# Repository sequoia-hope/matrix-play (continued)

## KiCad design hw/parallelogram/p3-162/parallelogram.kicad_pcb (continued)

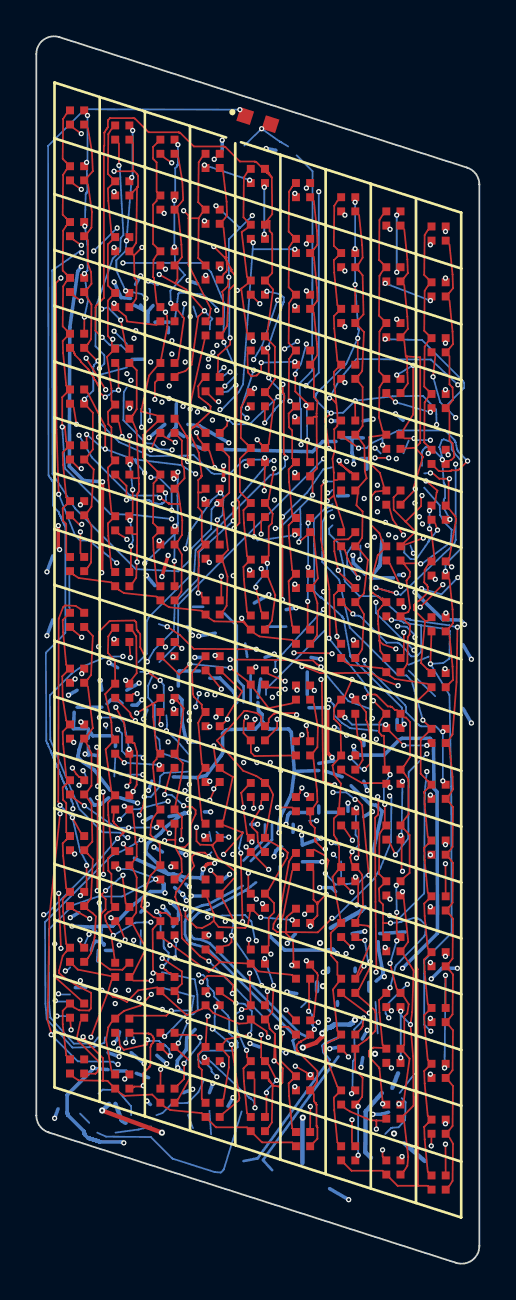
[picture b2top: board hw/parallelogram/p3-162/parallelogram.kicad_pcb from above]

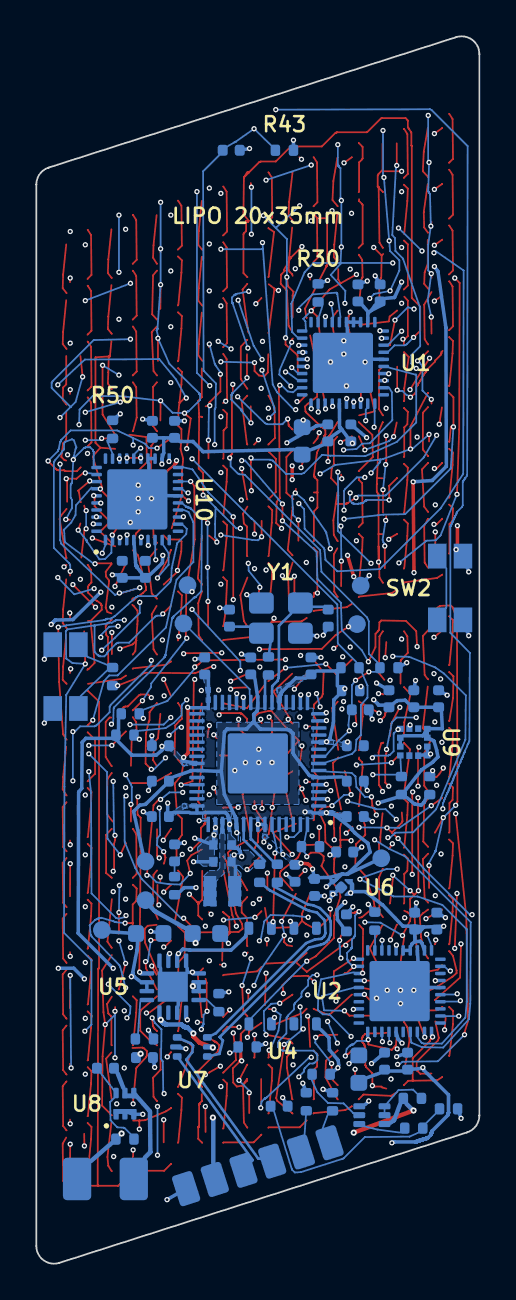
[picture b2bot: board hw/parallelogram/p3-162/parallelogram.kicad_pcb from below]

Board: 4 copper layers, 25.0 x 69.3 mm, 257 parts (94 on the bottom side), 134 nets.

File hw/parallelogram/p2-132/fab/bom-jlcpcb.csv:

Comment,Designator,Footprint,LCSC Part #,MPN,Manufacturer
1u,"C1,C3,C4,C31,C34,C41,C44",C_0402_1005Metric,C52923,CL05A105KA5NQNC,Samsung Electro-Mechanics
22u,"C2,C30,C40",C_0603_1608Metric,C86295,CL10A226MP8NUNE,Samsung Electro-Mechanics
10u,C5,C_0603_1608Metric,C19702,CL10A106KP8NNNC,Samsung Electro-Mechanics
100n,"C6,C7,C8,C9,C10,C11,C12,C13,C14,C20,C21,C22,C25,C27,C32,C33,C35,C42,C43,C70",C_0402_1005Metric,C1525,CL05B104KO5NNNC,Samsung Electro-Mechanics
4.7u,"C16,C18",C_0402_1005Metric_small_pads,C23733,CL05A475MP5NRNC,Samsung Electro-Mechanics
4.7u,"C17,C19,C26",C_0402_1005Metric,C23733,CL05A475MP5NRNC,Samsung Electro-Mechanics
15p,"C23,C24",C_0402_1005Metric,C1548,0402CG150J500NT,FH
RGB,"D1,D2,D3,D4,D5,D6,D7,D8,D9,D10,D11,D12,D13,D14,D15,D16,D17,D18,D19,D20,D21,D22,D23,D24,D25,D26,D27,D28,D29,D30,D31,D32,D33,D34,D35,D36,D37,D38,D39,D40,D41,D42,D43,D44,D45,D46,D47,D48,D49,D50,D51,D52,D53,D54,D55,D56,D57,D58,D59,D60,D61,D62,D63,D64,D65,D66,D67,D68,D69,D70,D71,D72,D73,D74,D75,D76,D77,D78,D79,D80,D81,D82,D83,D84,D85,D86,D87,D88,D89,D90,D91,D92,D93,D94,D95,D96,D97,D98,D99,D100,D101,D102,D103,D104,D105,D106,D107,D108,D109,D110,D111,D112,D113,D114,D115,D116,D117,D118,D119,D120,D121,D122,D123,D124,D125,D126,D127,D128,D129,D130,D131,D132",LED_XL-1615RGBC,C965840,XL-1615RGBC-RF,XINGLIGHT
3.3u,L1,L_pol_2016,C42411119,AOTA-B201610S3R3-101-T,Abracon
NTZD3155C,Q1,SOT-563,C236117,NTZD3155CT1G,onsemi
XYC-PT19C-L1,Q2,SENSOR_ALS-PT19,C2693594,XYC-PT19C-L1,NEWOPTO
5.1k,"R1,R2",R_0402_1005Metric,C25905,0402WGF5101TCE,UNI-ROYAL
10k,R3,R_0402_1005Metric,C25744,0402WGF1002TCE,UNI-ROYAL
3k,R4,R_0402_1005Metric,C25784,0402WGF3001TCE,UNI-ROYAL
3.6k,R5,R_0402_1005Metric,C25891,0402WGF3601TCE,UNI-ROYAL
100k,"R6,R7,R9,R10,R11,R12,R31",R_0402_1005Metric,C25741,0402WGF1003TCE,UNI-ROYAL
100R,R8,R_0402_1005Metric,C25076,0402WGF1000TCE,UNI-ROYAL
33R,R13,R_0402_1005Metric,C25105,0402WGF330JTCE,UNI-ROYAL
27R,"R14,R15",R_0402_1005Metric,C25100,0402WGF270JTCE,UNI-ROYAL
1k,"R16,R17,R18,R21,R22",R_0402_1005Metric,C11702,0402WGF1001TCE,UNI-ROYAL
4.7k,"R19,R20",R_0402_1005Metric,C25900,0402WGF4701TCE,UNI-ROYAL
30k,"R30,R33",R_0402_1005Metric,C25776,0402WGF3002TCE,UNI-ROYAL
22k,R43,R_0402_1005Metric,C25768,0402WGF2202TCE,UNI-ROYAL
USER / WAKE,SW1,SW_Panasonic_EVQP7J,C2828254,EVQP7J01P,PANASONIC
BOOTSEL,SW2,SW_Panasonic_EVQP7J,C2828254,EVQP7J01P,PANASONIC
AW20198QNR,"U1,U2",AW20198_QFN-40-1EP_5x5mm_P0.4mm_EP3.4x3.4mm,C5137654,AW20198QNR,Shanghai Awinic Tech
RP2350A,U3,RP2350-QFN-60-1EP_7x7_P0.4mm_EP3.4x3.4mm_ThermalVias,C42411118,RP2350A,Raspberry Pi
W25Q128JVPIQ,U4,WSON-8_6x5mm_P1.27mm_NoEPCopper,C190862,W25Q128JVPIQ,Winbond
BQ24073,U5,QFN-16-1EP_3x3mm_P0.5mm_EP1.7x1.7mm,C15220,BQ24073RGTR,Texas Instruments
TPS7A0233,U6,Texas_X2SON-4_1x1mm_P0.65mm,C2860046,TPS7A0233PDQNR,Texas Instruments
USBLC6-2P6,U7,SOT-666,C15999,USBLC6-2P6,STMicroelectronics
XB9901A,U8,XySemi_DFN-6_1.8x1.4mm,C669687,XB9901A,XySemi
LIS2DW12,U9,LGA-12_2x2mm_P0.5mm,C189624,LIS2DW12TR,STMicroelectronics
12MHz,Y1,Crystal_SMD_3225-4Pin_3.2x2.5mm,C20625731,ABM8-272-T3,Abracon

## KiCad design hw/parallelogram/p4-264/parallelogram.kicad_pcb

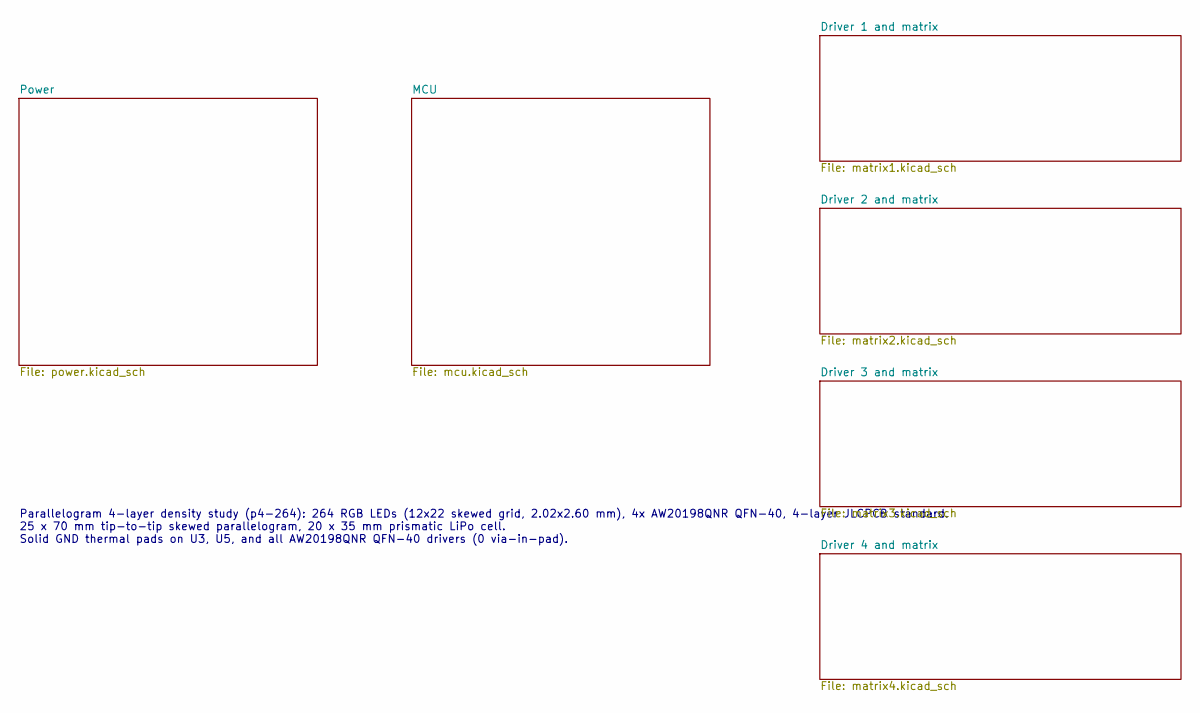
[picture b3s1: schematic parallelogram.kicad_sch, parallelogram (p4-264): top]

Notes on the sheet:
Parallelogram 4-layer density study (p4-264): 264 RGB LEDs (12x22 skewed grid, 2.02x2.60 mm), 4x AW20198QNR QFN-40, 4-layer JLCPCB standard. 25 x 70 mm tip-to-tip skewed parallelogram, 20 x 35 mm prismatic LiPo cell. Solid GND thermal pads on U3, U5, and all AW20198QNR QFN-40 drivers (0 via-in-pad).

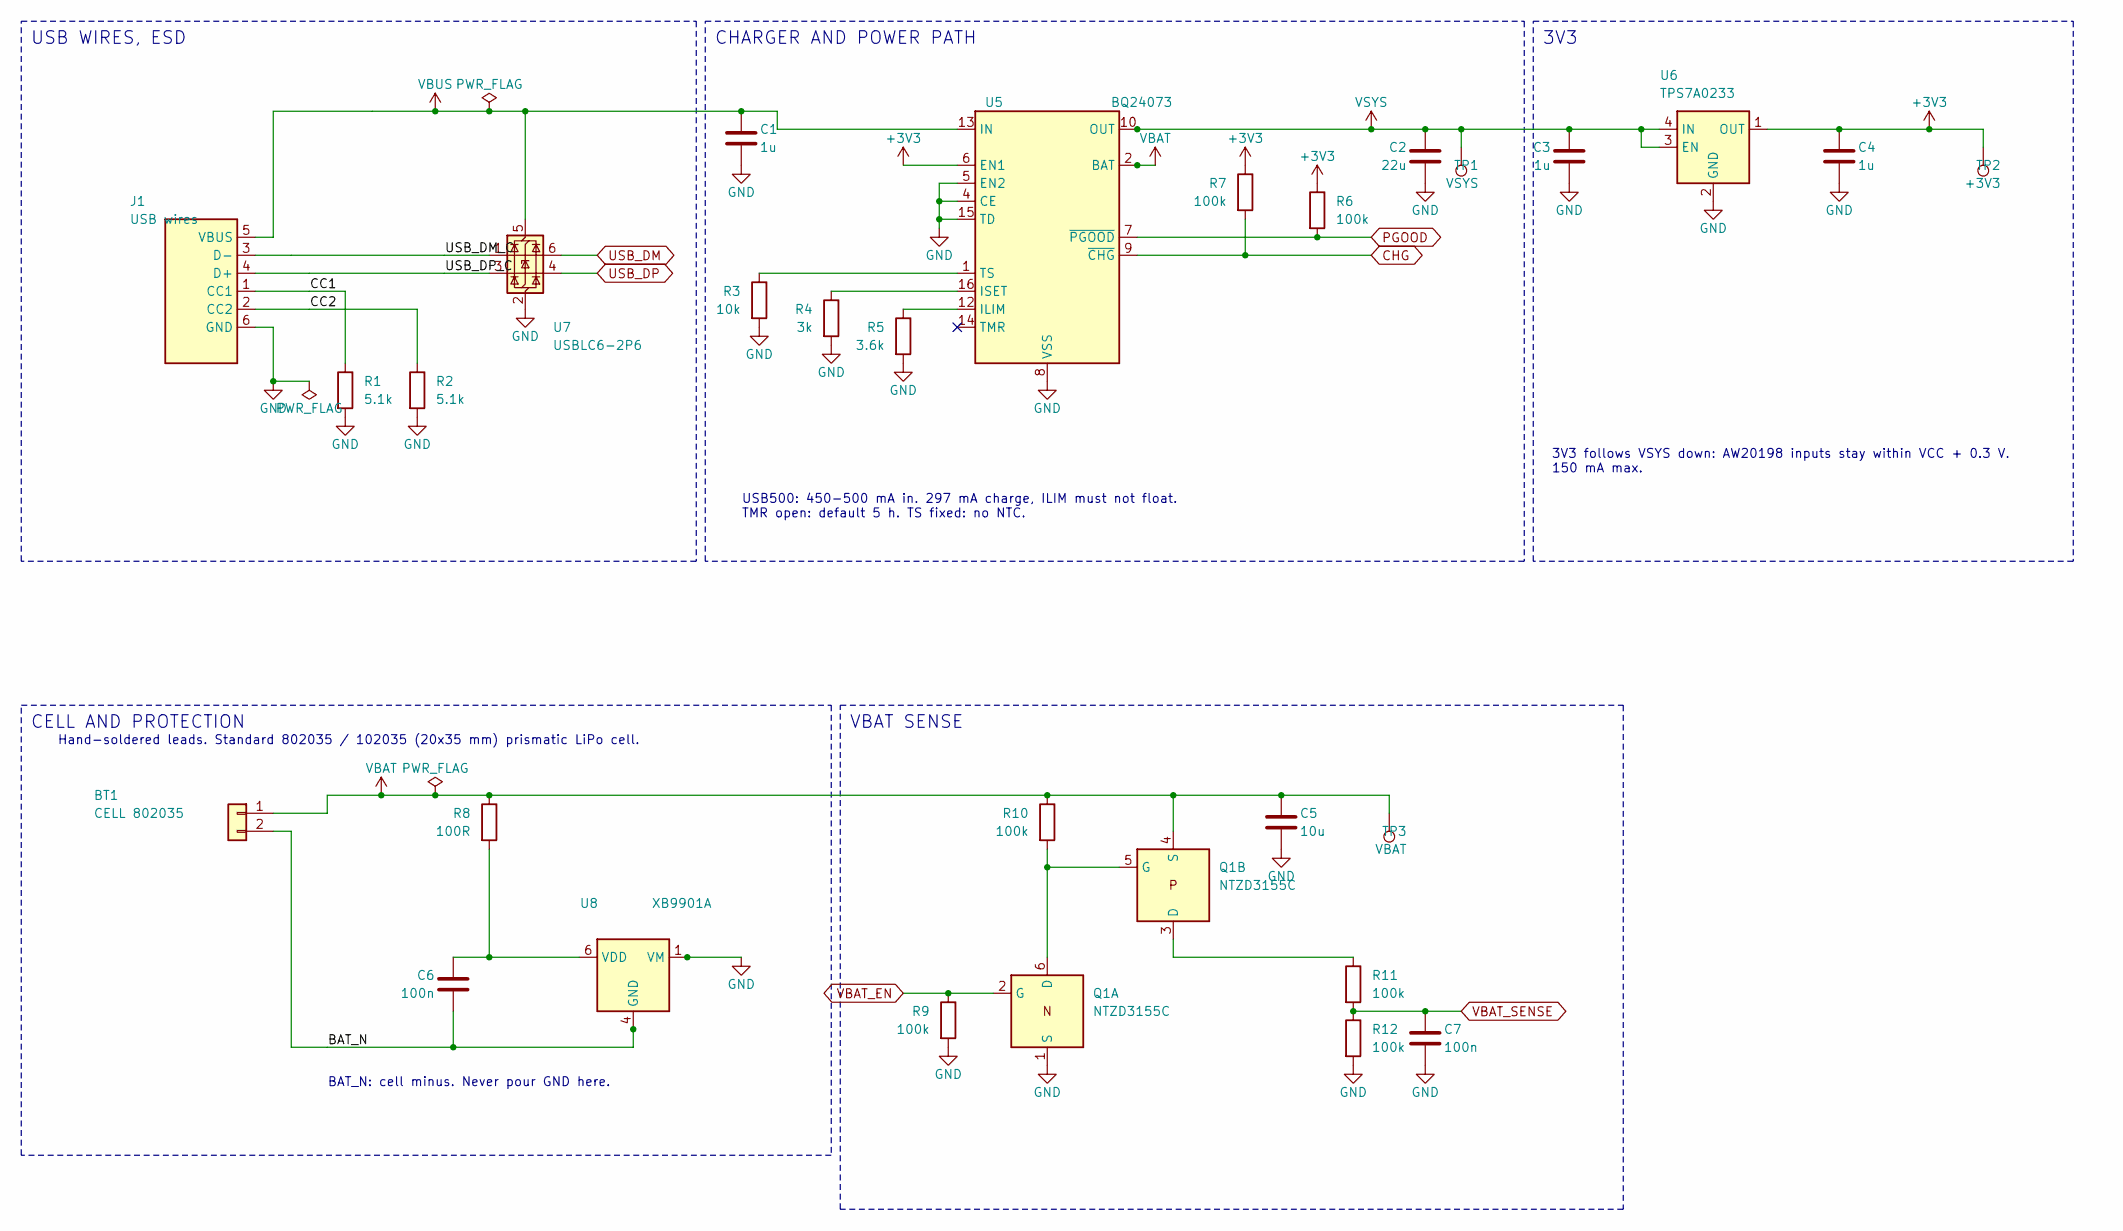
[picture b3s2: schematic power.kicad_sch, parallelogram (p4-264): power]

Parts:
BT1: CELL 802035; BatteryPads; MPN 802035
C1, C3, C4: 1u; C_0402_1005Metric; MPN CL05A105KA5NQNC; LCSC C52923
C2: 22u; C_0603_1608Metric; MPN CL10A226MP8NUNE; LCSC C86295
C5: 10u; C_0603_1608Metric; MPN CL10A106KP8NNNC; LCSC C19702
C6, C7: 100n; C_0402_1005Metric; MPN CL05B104KO5NNNC; LCSC C1525
J1: USB wires; USB_Pads; MPN none, wire pads
Q1: NTZD3155C; SOT-563; MPN NTZD3155CT1G; LCSC C236117
R1, R2: 5.1k; R_0402_1005Metric; MPN 0402WGF5101TCE; LCSC C25905
R3: 10k; R_0402_1005Metric; MPN 0402WGF1002TCE; LCSC C25744
R4: 3k; R_0402_1005Metric; MPN 0402WGF3001TCE; LCSC C25784
R5: 3.6k; R_0402_1005Metric; MPN 0402WGF3601TCE; LCSC C25891
R6, R7, R9, R10, R11, R12: 100k; R_0402_1005Metric; MPN 0402WGF1003TCE; LCSC C25741
R8: 100R; R_0402_1005Metric; MPN 0402WGF1000TCE; LCSC C25076
TP1: VSYS; TestPoint_Pad_D1.0mm
TP2: +3V3; TestPoint_Pad_D1.0mm
TP3: VBAT; TestPoint_Pad_D1.0mm
U5: BQ24073; QFN-16-1EP_3x3mm_P0.5mm_EP1.7x1.7mm; MPN BQ24073RGTR; LCSC C15220
U6: TPS7A0233; Texas_X2SON-4_1x1mm_P0.65mm; MPN TPS7A0233PDQNR; LCSC C2860046
U7: USBLC6-2P6; SOT-666; MPN USBLC6-2P6; LCSC C15999
U8: XB9901A; XySemi_DFN-6_1.8x1.4mm; MPN XB9901A; LCSC C669687

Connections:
+3V3: C4.1, R6.1, R7.1, TP2.1, U5.6 (EN1), U6.1 (OUT); also elsewhere on the board
/Power/BAT_N: BT1.2, C6.2, U8.4 (GND), U8.5 (GND)
/Power/CC1: J1.1 (CC1), R1.1
/Power/CC2: J1.2 (CC2), R2.1
/Power/USB_DM_C: J1.3 (D-), U7.1 (I/O1)
/Power/USB_DP_C: J1.4 (D+), U7.3 (I/O2)
CHG: R7.2, U5.9 (~CHG); also elsewhere on the board
unnamed: Q1.5 (G), Q1.6 (D), R10.2
unnamed: Q1.3 (D), R11.1
unnamed: R5.1, U5.12 (ILIM)
unnamed: R4.1, U5.16 (ISET)
unnamed: R3.1, U5.1 (TS)
unnamed: C6.1, R8.2, U8.6 (VDD)
PGOOD: R6.2, U5.7 (~PGOOD); also elsewhere on the board
USB_DM: U7.6 (I/O1); also elsewhere on the board
USB_DP: U7.4 (I/O2); also elsewhere on the board
VBAT_EN: Q1.2 (G), R9.1; also elsewhere on the board
VBAT_SENSE: C7.1, R11.2, R12.1; also elsewhere on the board
VSYS: C2.1, C3.1, TP1.1, U5.10 (OUT), U5.11 (OUT), U6.3 (EN), U6.4 (IN); also elsewhere on the board

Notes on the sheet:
USB WIRES, ESD
USB500: 450-500 mA in. 297 mA charge, ILIM must not float. TMR open: default 5 h. TS fixed: no NTC.
CHARGER AND POWER PATH
3V3 follows VSYS down: AW20198 inputs stay within VCC + 0.3 V. 150 mA max.
3V3
Hand-soldered leads. Standard 802035 / 102035 (20x35 mm) prismatic LiPo cell.
BAT_N: cell minus. Never pour GND here.
CELL AND PROTECTION
VBAT SENSE

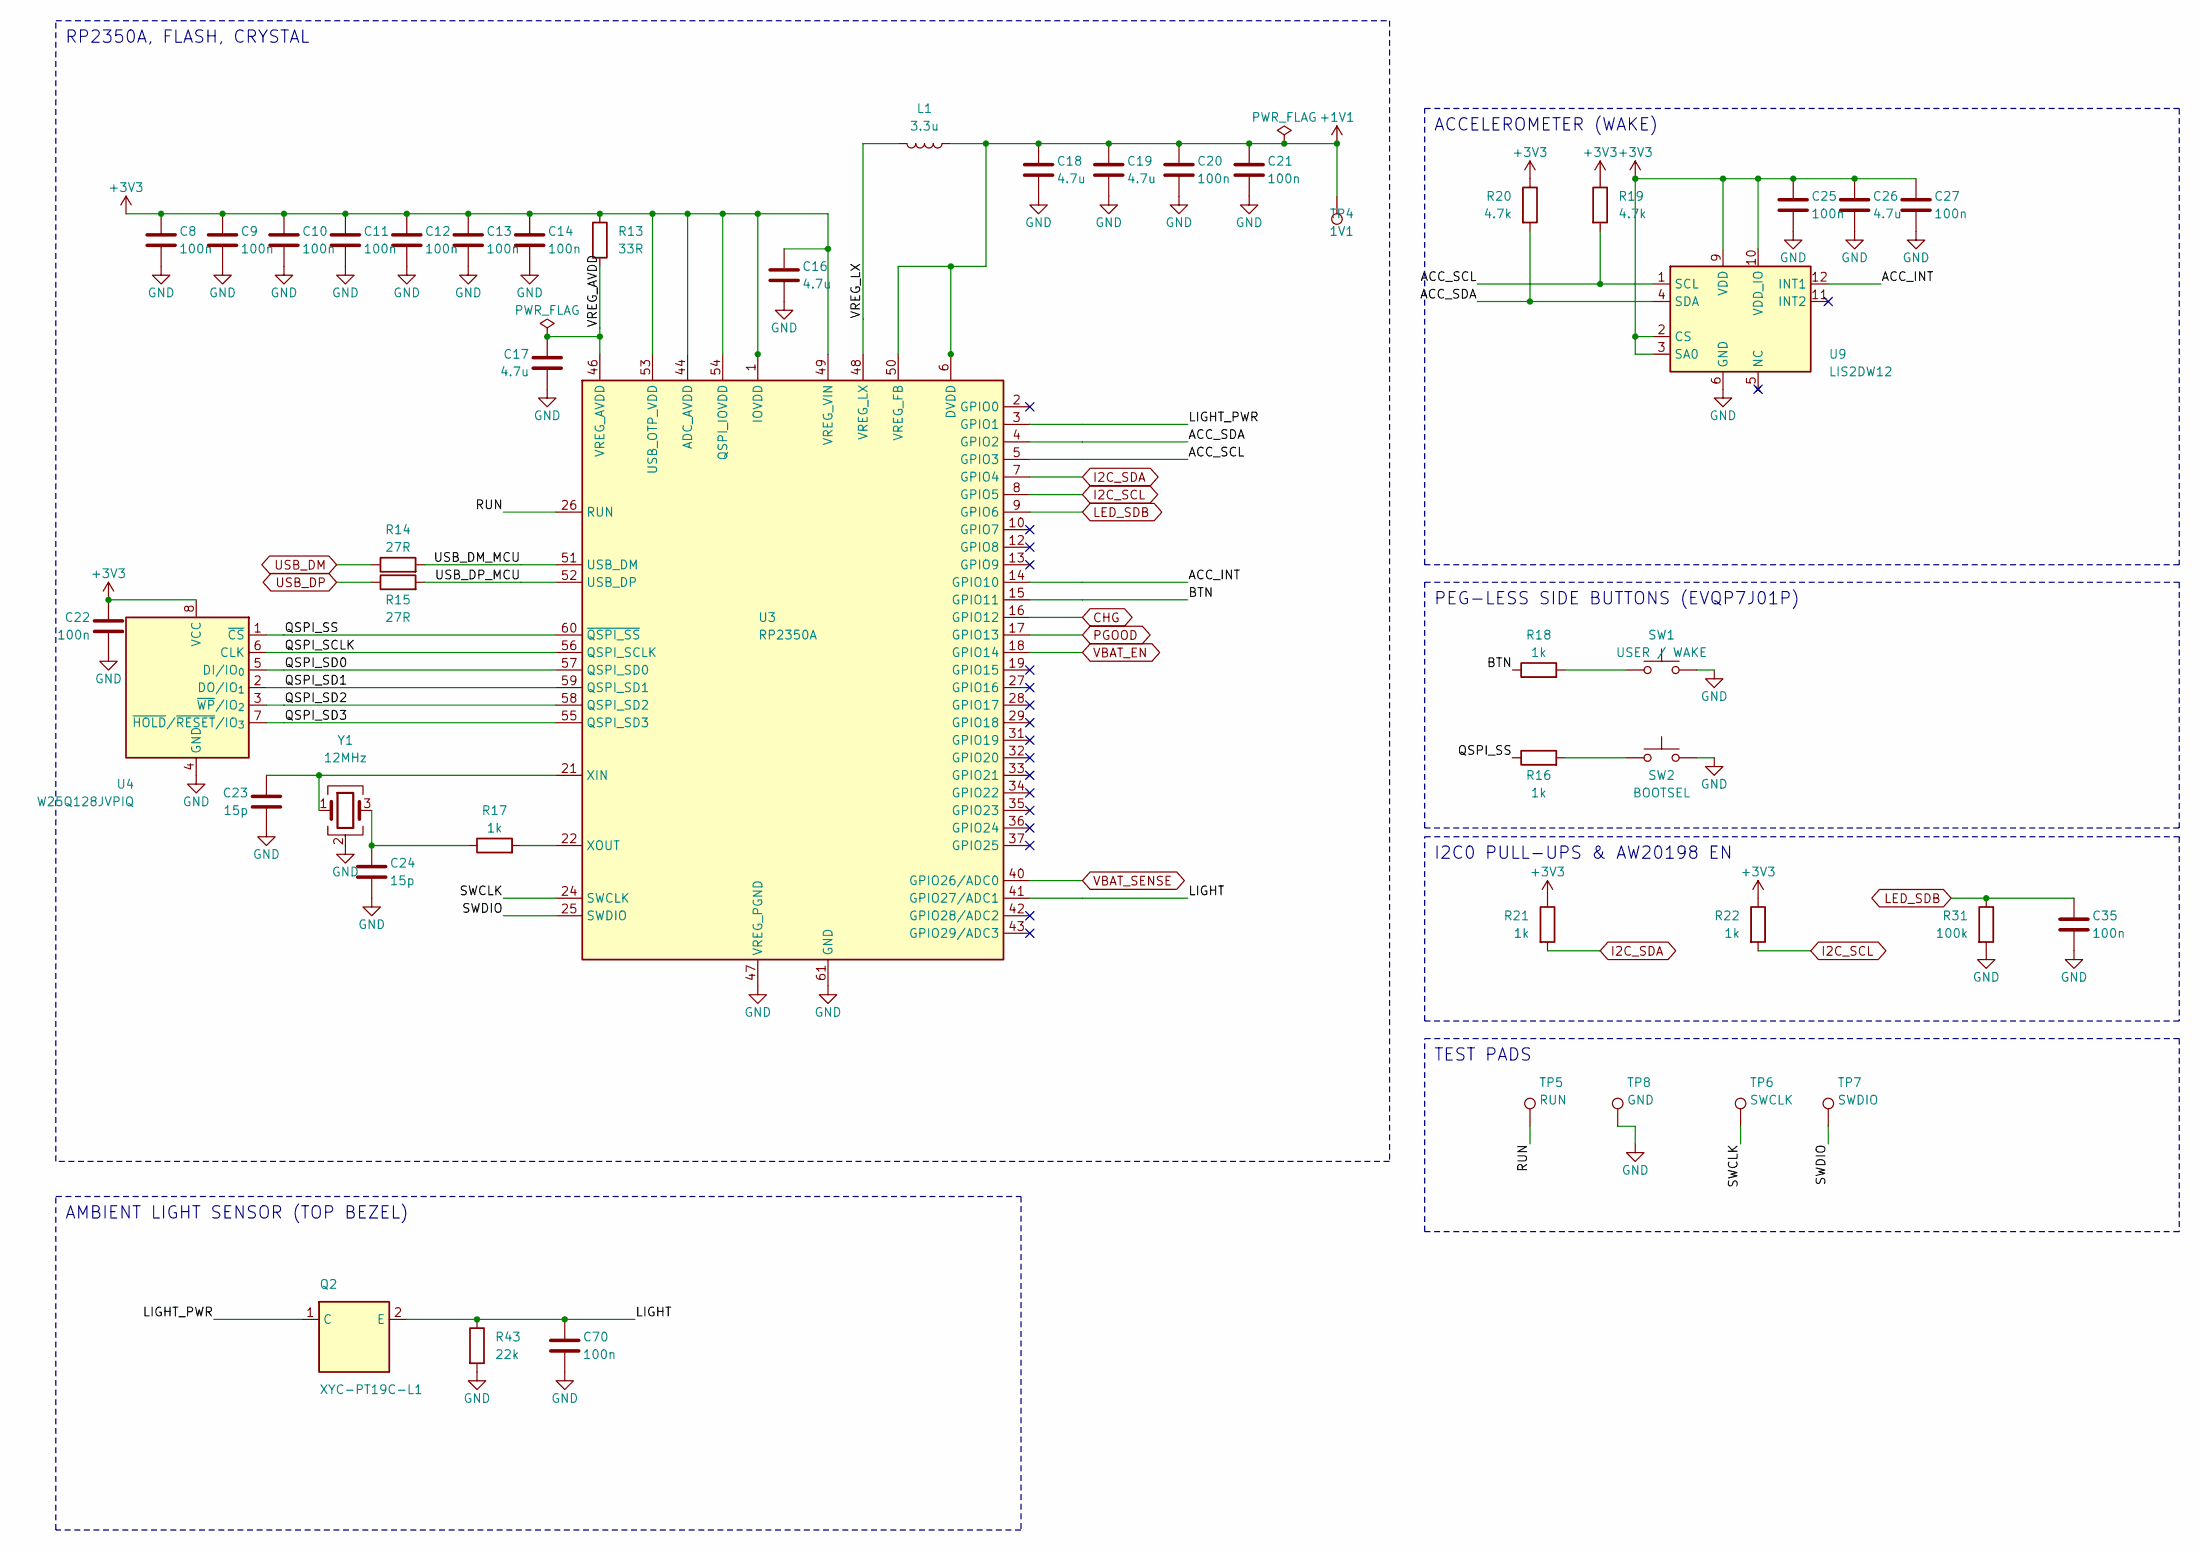
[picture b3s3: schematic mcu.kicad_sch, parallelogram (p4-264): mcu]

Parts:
C8, C9, C10, C11, C12, C13, C14, C20, C21, C22, C25, C27, C35, C70: 100n; C_0402_1005Metric; MPN CL05B104KO5NNNC; LCSC C1525
C16, C18: 4.7u; C_0402_1005Metric_small_pads; MPN CL05A475MP5NRNC; LCSC C23733
C17, C19, C26: 4.7u; C_0402_1005Metric; MPN CL05A475MP5NRNC; LCSC C23733
C23, C24: 15p; C_0402_1005Metric; MPN 0402CG150J500NT; LCSC C1548
L1: 3.3u; L_pol_2016; MPN AOTA-B201610S3R3-101-T; LCSC C42411119
Q2: XYC-PT19C-L1; SENSOR_ALS-PT19; MPN XYC-PT19C-L1; LCSC C2693594
R13: 33R; R_0402_1005Metric; MPN 0402WGF330JTCE; LCSC C25105
R14, R15: 27R; R_0402_1005Metric; MPN 0402WGF270JTCE; LCSC C25100
R16, R17, R18, R21, R22: 1k; R_0402_1005Metric; MPN 0402WGF1001TCE; LCSC C11702
R19, R20: 4.7k; R_0402_1005Metric; MPN 0402WGF4701TCE; LCSC C25900
R31: 100k; R_0402_1005Metric; MPN 0402WGF1003TCE; LCSC C25741
R43: 22k; R_0402_1005Metric; MPN 0402WGF2202TCE; LCSC C25768
SW1: USER / WAKE; SW_Panasonic_EVQP7J; MPN EVQP7J01P; LCSC C2828254
SW2: BOOTSEL; SW_Panasonic_EVQP7J; MPN EVQP7J01P; LCSC C2828254
TP4: 1V1; TestPoint_Pad_D1.0mm
TP5: RUN; TestPoint_Pad_D1.0mm
TP6: SWCLK; TestPoint_Pad_D1.0mm
TP7: SWDIO; TestPoint_Pad_D1.0mm
TP8: GND; TestPoint_Pad_D1.0mm
U3: RP2350A; RP2350-QFN-60-1EP_7x7_P0.4mm_EP3.4x3.4mm_ThermalVias; MPN RP2350A; LCSC C42411118
U4: W25Q128JVPIQ; WSON-8_6x5mm_P1.27mm_NoEPCopper; MPN W25Q128JVPIQ; LCSC C190862
U9: LIS2DW12; LGA-12_2x2mm_P0.5mm; MPN LIS2DW12TR; LCSC C189624
Y1: 12MHz; Crystal_SMD_3225-4Pin_3.2x2.5mm; MPN ABM8-272-T3; LCSC C20625731

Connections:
+3V3: C8.1, C9.1, C10.1, C11.1, C12.1, C13.1, C14.1, C16.1, C22.1, C25.1, C26.1, C27.1, R13.1, R19.1, R20.1, R21.1, R22.1, U3.1 (IOVDD), U3.11 (IOVDD), U3.20 (IOVDD), U3.30 (IOVDD), U3.38 (IOVDD), U3.44 (ADC_AVDD), U3.45 (IOVDD), U3.49 (VREG_VIN), U3.53 (USB_OTP_VDD), U3.54 (QSPI_IOVDD), U4.8 (VCC), U9.2 (CS), U9.3 (SA0), U9.9 (VDD), U9.10 (VDD_IO); also elsewhere on the board
/MCU/ACC_INT: U3.14 (GPIO10), U9.12 (INT1)
/MCU/ACC_SCL: R19.2, U3.5 (GPIO3), U9.1 (SCL)
/MCU/ACC_SDA: R20.2, U3.4 (GPIO2), U9.4 (SDA)
/MCU/BTN: R18.1, U3.15 (GPIO11)
/MCU/LIGHT: C70.1, Q2.2 (E), R43.1, U3.41 (GPIO27/ADC1)
/MCU/LIGHT_PWR: Q2.1 (C), U3.3 (GPIO1)
/MCU/QSPI_SCLK: U3.56 (QSPI_SCLK), U4.6 (CLK)
/MCU/QSPI_SD0: U3.57 (QSPI_SD0), U4.5 (DI/IO_{0})
/MCU/QSPI_SD1: U3.59 (QSPI_SD1), U4.2 (DO/IO_{1})
/MCU/QSPI_SD2: U3.58 (QSPI_SD2), U4.3 (~WP/IO_{2})
/MCU/QSPI_SD3: U3.55 (QSPI_SD3), U4.7 (~HOLD/~RESET/IO_{3})
/MCU/QSPI_SS: R16.1, U3.60 (~QSPI_SS), U4.1 (~CS)
/MCU/RUN: TP5.1, U3.26 (RUN)
/MCU/SWCLK: TP6.1, U3.24 (SWCLK)
/MCU/SWDIO: TP7.1, U3.25 (SWDIO)
/MCU/USB_DM_MCU: R14.2, U3.51 (USB_DM)
/MCU/USB_DP_MCU: R15.2, U3.52 (USB_DP)
/MCU/VREG_LX: L1.2, U3.48 (VREG_LX)
CHG: U3.16 (GPIO12); also elsewhere on the board
I2C_SCL: R22.2, U3.8 (GPIO5); also elsewhere on the board
I2C_SDA: R21.2, U3.7 (GPIO4); also elsewhere on the board
LED_SDB: C35.1, R31.1, U3.9 (GPIO6); also elsewhere on the board
unnamed: C24.1, R17.1, Y1.3
unnamed: R16.2, SW2.1
unnamed: R18.2, SW1.1
unnamed: C23.1, U3.21 (XIN), Y1.1
unnamed: R17.2, U3.22 (XOUT)
PGOOD: U3.17 (GPIO13); also elsewhere on the board
USB_DM: R14.1; also elsewhere on the board
USB_DP: R15.1; also elsewhere on the board
VBAT_EN: U3.18 (GPIO14); also elsewhere on the board
VBAT_SENSE: U3.40 (GPIO26/ADC0); also elsewhere on the board

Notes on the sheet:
RP2350A, FLASH, CRYSTAL
ACCELEROMETER (WAKE)
PEG-LESS SIDE BUTTONS (EVQP7J01P)
I2C0 PULL-UPS & AW20198 EN
TEST PADS
AMBIENT LIGHT SENSOR (TOP BEZEL)

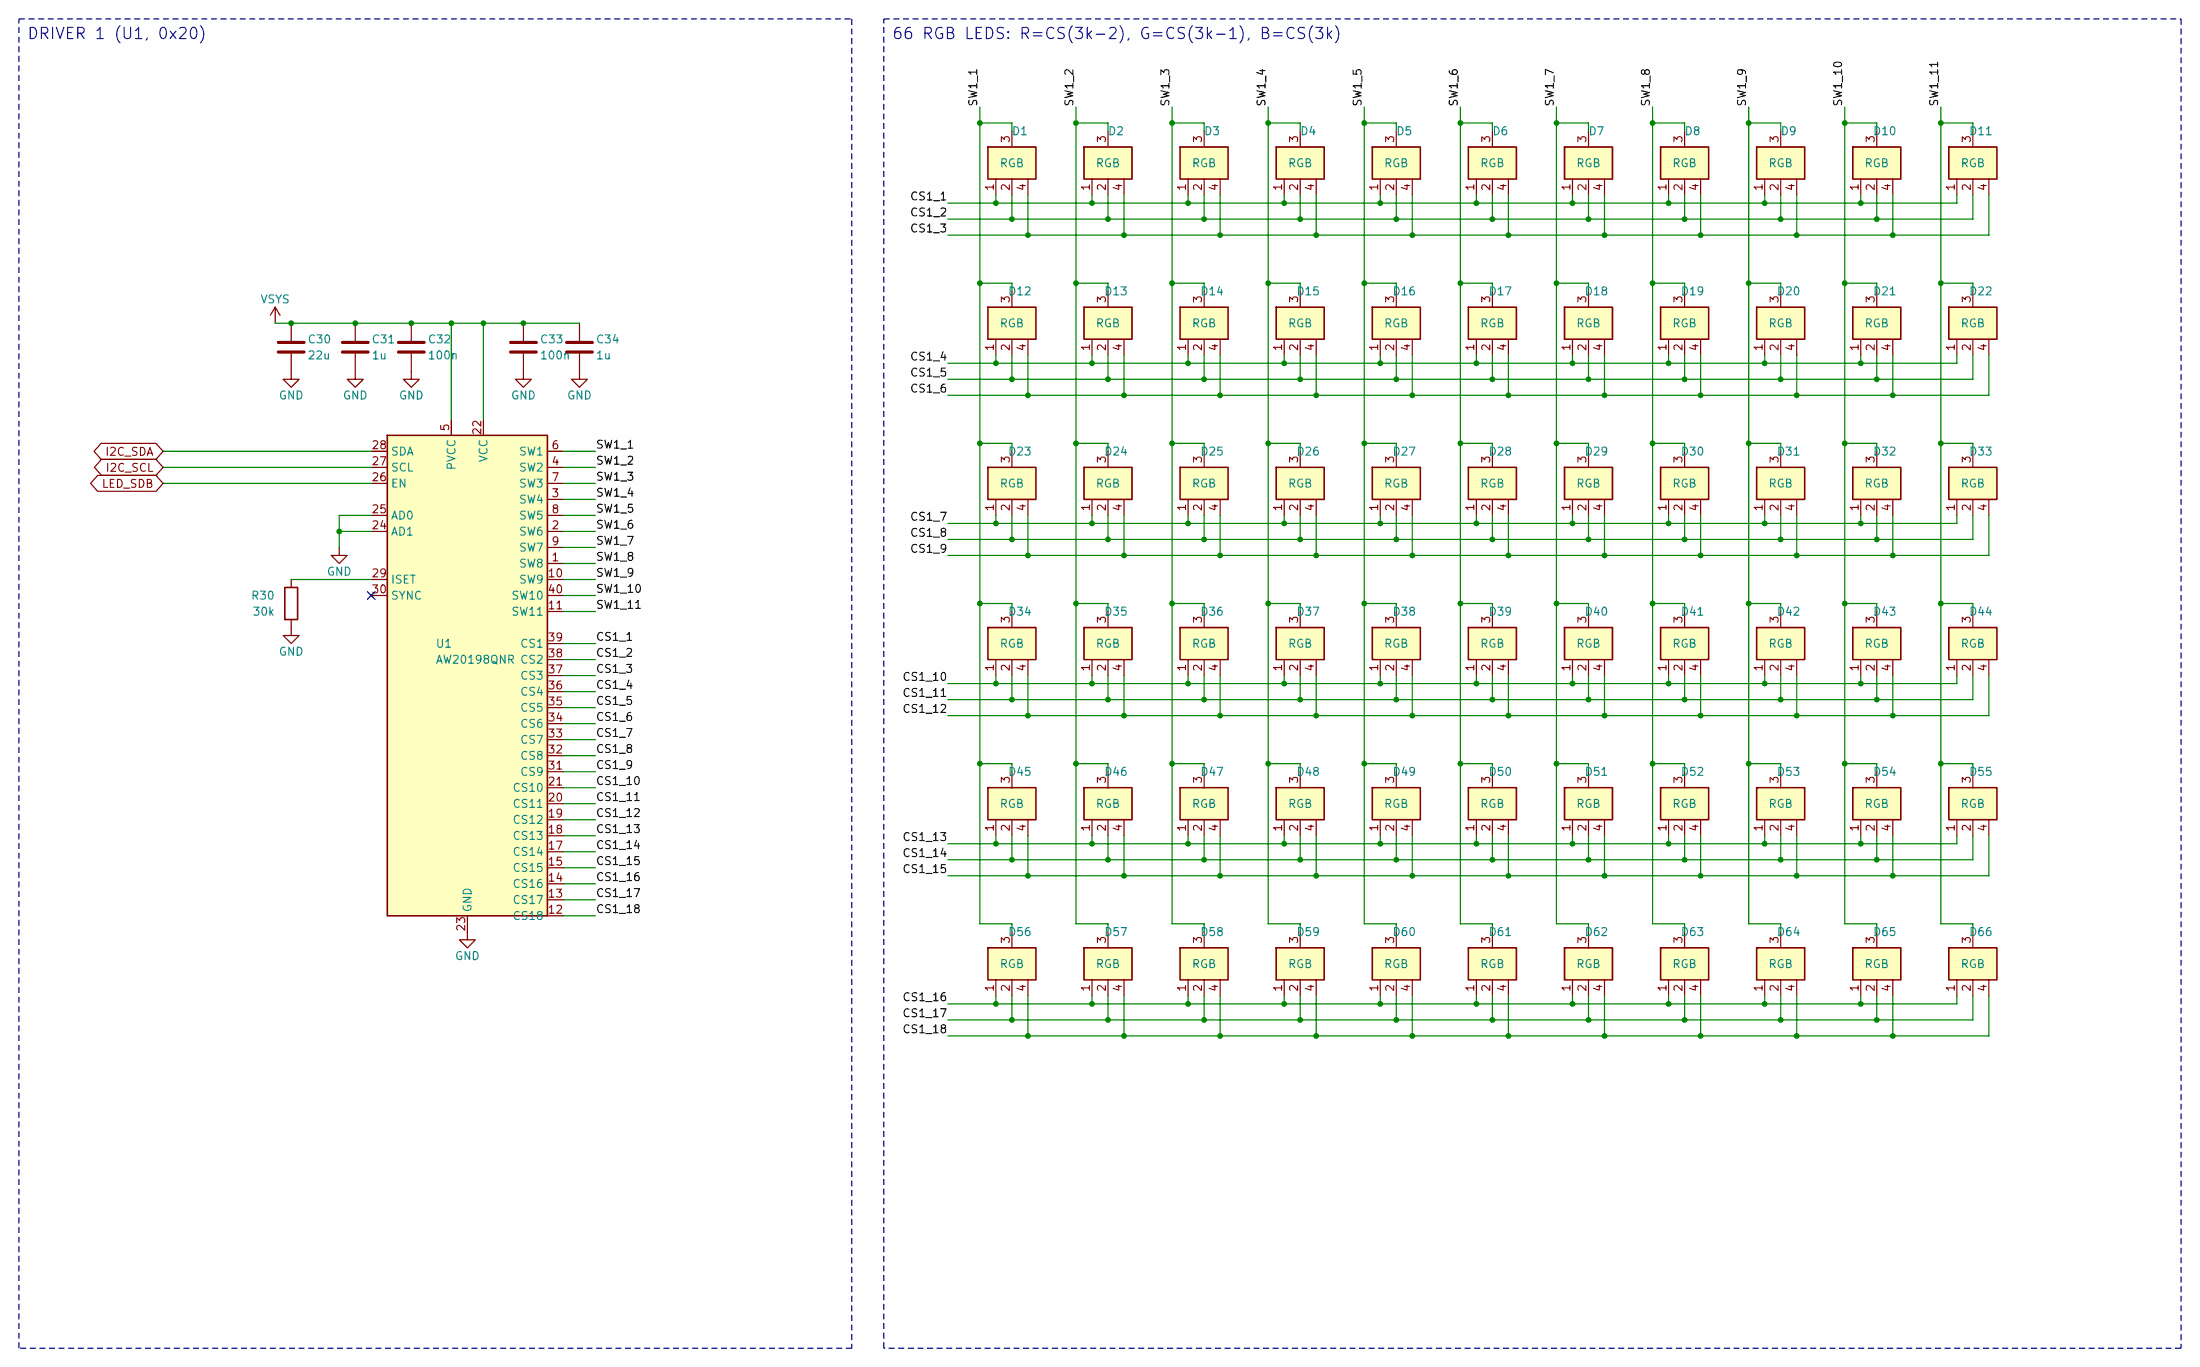
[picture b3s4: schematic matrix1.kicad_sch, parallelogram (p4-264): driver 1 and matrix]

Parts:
C30: 22u; C_0603_1608Metric; MPN CL10A226MP8NUNE; LCSC C86295
C31, C34: 1u; C_0402_1005Metric; MPN CL05A105KA5NQNC; LCSC C52923
C32, C33: 100n; C_0402_1005Metric; MPN CL05B104KO5NNNC; LCSC C1525
D1, D2, D3, D4, D5, D6, D7, D8, D9, D10, D11, D12, D13, D14, D15, D16, D17, D18, D19, D20, D21, D22, D23, D24, D25, D26, D27, D28, D29, D30, D31, D32, D33, D34, D35, D36, D37, D38, D39, D40, D41, D42, D43, D44, D45, D46, D47, D48, D49, D50, D51, D52, D53, D54, D55, D56, D57, D58, D59, D60, D61, D62, D63, D64, D65, D66: RGB; LED_XL-1010RGB; MPN XL-1010RGB-YG; LCSC C965834
R30: 30k; R_0402_1005Metric; MPN 0402WGF3002TCE; LCSC C25776
U1: AW20198QNR; AW20198_QFN-40-1EP_5x5mm_P0.4mm_EP3.4x3.4mm; MPN AW20198QNR; LCSC C5137654

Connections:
/Driver 1 and matrix/CS1_1: D1.1 (R), D2.1 (R), D3.1 (R), D4.1 (R), D5.1 (R), D6.1 (R), D7.1 (R), D8.1 (R), D9.1 (R), D10.1 (R), D11.1 (R), U1.39 (CS1)
/Driver 1 and matrix/CS1_2: D1.2 (G), D2.2 (G), D3.2 (G), D4.2 (G), D5.2 (G), D6.2 (G), D7.2 (G), D8.2 (G), D9.2 (G), D10.2 (G), D11.2 (G), U1.38 (CS2)
/Driver 1 and matrix/CS1_3: D1.4 (B), D2.4 (B), D3.4 (B), D4.4 (B), D5.4 (B), D6.4 (B), D7.4 (B), D8.4 (B), D9.4 (B), D10.4 (B), D11.4 (B), U1.37 (CS3)
/Driver 1 and matrix/CS1_4: D12.1 (R), D13.1 (R), D14.1 (R), D15.1 (R), D16.1 (R), D17.1 (R), D18.1 (R), D19.1 (R), D20.1 (R), D21.1 (R), D22.1 (R), U1.36 (CS4)
/Driver 1 and matrix/CS1_5: D12.2 (G), D13.2 (G), D14.2 (G), D15.2 (G), D16.2 (G), D17.2 (G), D18.2 (G), D19.2 (G), D20.2 (G), D21.2 (G), D22.2 (G), U1.35 (CS5)
/Driver 1 and matrix/CS1_6: D12.4 (B), D13.4 (B), D14.4 (B), D15.4 (B), D16.4 (B), D17.4 (B), D18.4 (B), D19.4 (B), D20.4 (B), D21.4 (B), D22.4 (B), U1.34 (CS6)
/Driver 1 and matrix/CS1_7: D23.1 (R), D24.1 (R), D25.1 (R), D26.1 (R), D27.1 (R), D28.1 (R), D29.1 (R), D30.1 (R), D31.1 (R), D32.1 (R), D33.1 (R), U1.33 (CS7)
/Driver 1 and matrix/CS1_8: D23.2 (G), D24.2 (G), D25.2 (G), D26.2 (G), D27.2 (G), D28.2 (G), D29.2 (G), D30.2 (G), D31.2 (G), D32.2 (G), D33.2 (G), U1.32 (CS8)
/Driver 1 and matrix/CS1_9: D23.4 (B), D24.4 (B), D25.4 (B), D26.4 (B), D27.4 (B), D28.4 (B), D29.4 (B), D30.4 (B), D31.4 (B), D32.4 (B), D33.4 (B), U1.31 (CS9)
/Driver 1 and matrix/CS1_10: D34.1 (R), D35.1 (R), D36.1 (R), D37.1 (R), D38.1 (R), D39.1 (R), D40.1 (R), D41.1 (R), D42.1 (R), D43.1 (R), D44.1 (R), U1.21 (CS10)
/Driver 1 and matrix/CS1_11: D34.2 (G), D35.2 (G), D36.2 (G), D37.2 (G), D38.2 (G), D39.2 (G), D40.2 (G), D41.2 (G), D42.2 (G), D43.2 (G), D44.2 (G), U1.20 (CS11)
/Driver 1 and matrix/CS1_12: D34.4 (B), D35.4 (B), D36.4 (B), D37.4 (B), D38.4 (B), D39.4 (B), D40.4 (B), D41.4 (B), D42.4 (B), D43.4 (B), D44.4 (B), U1.19 (CS12)
/Driver 1 and matrix/CS1_13: D45.1 (R), D46.1 (R), D47.1 (R), D48.1 (R), D49.1 (R), D50.1 (R), D51.1 (R), D52.1 (R), D53.1 (R), D54.1 (R), D55.1 (R), U1.18 (CS13)
/Driver 1 and matrix/CS1_14: D45.2 (G), D46.2 (G), D47.2 (G), D48.2 (G), D49.2 (G), D50.2 (G), D51.2 (G), D52.2 (G), D53.2 (G), D54.2 (G), D55.2 (G), U1.17 (CS14)
/Driver 1 and matrix/CS1_15: D45.4 (B), D46.4 (B), D47.4 (B), D48.4 (B), D49.4 (B), D50.4 (B), D51.4 (B), D52.4 (B), D53.4 (B), D54.4 (B), D55.4 (B), U1.15 (CS15)
/Driver 1 and matrix/CS1_16: D56.1 (R), D57.1 (R), D58.1 (R), D59.1 (R), D60.1 (R), D61.1 (R), D62.1 (R), D63.1 (R), D64.1 (R), D65.1 (R), D66.1 (R), U1.14 (CS16)
/Driver 1 and matrix/CS1_17: D56.2 (G), D57.2 (G), D58.2 (G), D59.2 (G), D60.2 (G), D61.2 (G), D62.2 (G), D63.2 (G), D64.2 (G), D65.2 (G), D66.2 (G), U1.13 (CS17)
/Driver 1 and matrix/CS1_18: D56.4 (B), D57.4 (B), D58.4 (B), D59.4 (B), D60.4 (B), D61.4 (B), D62.4 (B), D63.4 (B), D64.4 (B), D65.4 (B), D66.4 (B), U1.12 (CS18)
/Driver 1 and matrix/SW1_1: D1.3 (A), D12.3 (A), D23.3 (A), D34.3 (A), D45.3 (A), D56.3 (A), U1.6 (SW1)
/Driver 1 and matrix/SW1_2: D2.3 (A), D13.3 (A), D24.3 (A), D35.3 (A), D46.3 (A), D57.3 (A), U1.4 (SW2)
/Driver 1 and matrix/SW1_3: D3.3 (A), D14.3 (A), D25.3 (A), D36.3 (A), D47.3 (A), D58.3 (A), U1.7 (SW3)
/Driver 1 and matrix/SW1_4: D4.3 (A), D15.3 (A), D26.3 (A), D37.3 (A), D48.3 (A), D59.3 (A), U1.3 (SW4)
/Driver 1 and matrix/SW1_5: D5.3 (A), D16.3 (A), D27.3 (A), D38.3 (A), D49.3 (A), D60.3 (A), U1.8 (SW5)
/Driver 1 and matrix/SW1_6: D6.3 (A), D17.3 (A), D28.3 (A), D39.3 (A), D50.3 (A), D61.3 (A), U1.2 (SW6)
/Driver 1 and matrix/SW1_7: D7.3 (A), D18.3 (A), D29.3 (A), D40.3 (A), D51.3 (A), D62.3 (A), U1.9 (SW7)
/Driver 1 and matrix/SW1_8: D8.3 (A), D19.3 (A), D30.3 (A), D41.3 (A), D52.3 (A), D63.3 (A), U1.1 (SW8)
/Driver 1 and matrix/SW1_9: D9.3 (A), D20.3 (A), D31.3 (A), D42.3 (A), D53.3 (A), D64.3 (A), U1.10 (SW9)
/Driver 1 and matrix/SW1_10: D10.3 (A), D21.3 (A), D32.3 (A), D43.3 (A), D54.3 (A), D65.3 (A), U1.40 (SW10)
/Driver 1 and matrix/SW1_11: D11.3 (A), D22.3 (A), D33.3 (A), D44.3 (A), D55.3 (A), D66.3 (A), U1.11 (SW11)
I2C_SCL: U1.27 (SCL); also elsewhere on the board
I2C_SDA: U1.28 (SDA); also elsewhere on the board
LED_SDB: U1.26 (EN); also elsewhere on the board
unnamed: R30.1, U1.29 (ISET)
VSYS: C30.1, C31.1, C32.1, C33.1, C34.1, U1.5 (PVCC), U1.22 (VCC); also elsewhere on the board

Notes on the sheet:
DRIVER 1 (U1, 0x20)
66 RGB LEDS: R=CS(3k-2), G=CS(3k-1), B=CS(3k)
